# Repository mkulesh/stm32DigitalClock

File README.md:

#  "A digital clock based on STM32F405 MCU"

This repository provides hardware layout and firmware for a radio-controlled digital clock based on [STM32F405RG](http://www.st.com/content/st_com/en/products/microcontrollers/stm32-32-bit-arm-cortex-mcus/stm32-high-performance-mcus/stm32f4-series/stm32f405-415/stm32f405rg.html) MCU and [DCF77](https://de.wikipedia.org/wiki/DCF77) receiver:

## Hardware design
This clock consist of two boards:
- the first display board contains four 0.8 inch. single digit numerical displays, one 2x16 chars LCD-display, and four buttons that allow to adjust current time, three alarms and some settings:

- the second board contains STM32F405 MCU with a lot of periphery: DC connector, voltage regulators, HSE and LSE crystals, JTAG programming connector, light sensor, temperature sensor, DCF77 receiver with ferrite core, SD card connector, DAC and audio amplifier for primary WAV-based alarm, outputs for audio speakers, one piezo buzzer for the secondary alarm, UART-USB bridge and USB connector (used for debugging purposes):

PCB are developed in Eagle CAD (see directory pcb):

## Firmware
The firmware (see directory src) is written in C++ [System Workbench for STM32](http://www.st.com/en/development-tools/sw4stm32.html). It is based on HAL library, FatFS and the second object-oriented abstraction layer called *StmPlusPlus* that implements high-level access for all used hardware components. *StmPlusPlus* also contains WAV-streamer (16 bit stereo, 44kHz) and [DCF77](https://de.wikipedia.org/wiki/DCF77) receiver with a special windowed filter used to improce signal quality.

## There are some known problems in this project
- DCF77 receiver heeds some time a pair of hours to capture the time stamp. 
- Wrong position of the DC and USB connector: access to the connector is blocked by audio speakers
- Level of the input signal for the audio amplifier is too high. 

## License
This software is published under the *GNU General Public License, Version 3*

Copyright (C) 2016-2017 Mikhail Kulesh

This program is free software: you can redistribute it and/or modify it under the terms of the GNU General Public License as published by the Free Software Foundation, either version 3 of the License, or (at your option) any later version.

This program is distributed in the hope that it will be useful, but WITHOUT ANY WARRANTY; without even the implied warranty of MERCHANTABILITY or FITNESS FOR A PARTICULAR PURPOSE.  See the GNU General Public License for more details. You should have received a copy of the GNU General Public License along with this program.

If not, see [www.gnu.org/licenses](http://www.gnu.org/licenses).

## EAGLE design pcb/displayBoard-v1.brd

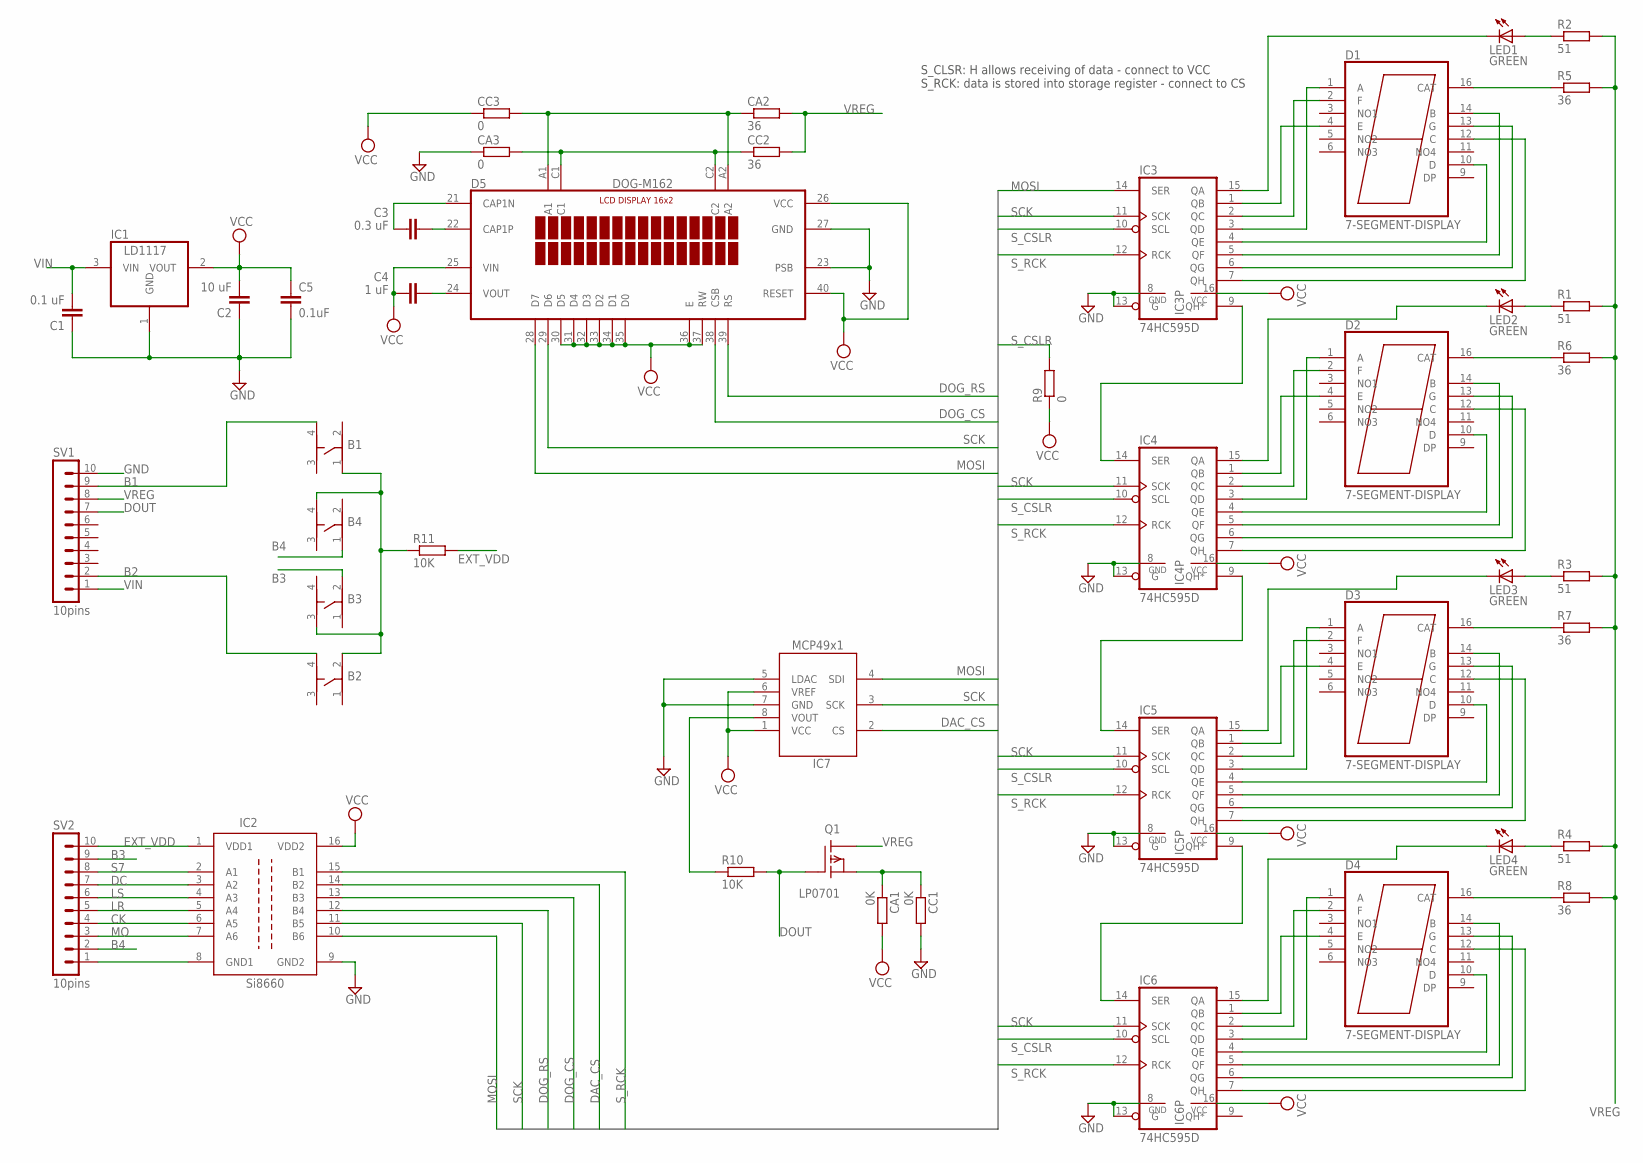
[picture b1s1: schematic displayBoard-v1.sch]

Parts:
B1, B2, B3, B4: BUTTON-D6X
C1: 0.1 uF; C1206
C2: 10 uF; C1206
C3: 0.3 uF; C1206
C4: 1 uF; C1206
C5: 0.1uF; C1206
CA1: 0K; R1206
CA2: 36; R1206
CA3: 0; R1206
CC1: 0K; R1206
CC2: 36; R1206
CC3: 0; R1206
D1, D2, D3, D4: 7-SEGMENT-DISPLAY; LDS-A812
D5: DOG-M162; DOGM162
IC1: LD1117; SOT223
IC2: SI-8660; SOP-16
IC3, IC4, IC5, IC6: 74HC595D; SO16
IC7: MCP4921; MSOP-8
LED1, LED2, LED3, LED4: GREEN; LED3MM
Q1: LP0701; TO-92
R1, R2, R3, R4: 51; R1206
R5, R6, R7, R8: 36; R1206
R9: 0; R1206
R10, R11: 10K; R1206
SV1, SV2: 10pins; MA10-1

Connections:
B1: B1.4, SV1.9
B2: B2.4, SV1.2
B3: B3.2, SV2.9
B4: B4.1, SV2.2
CK: IC2.6 (A5), SV2.4
DAC_CS: IC2.14 (B2), IC7.2 (CS)
DC: IC2.3 (A2), SV2.7
DOG_CS: D5.38 (CSB), IC2.13 (B3)
DOG_RS: D5.39 (RS), IC2.12 (B4)
DOUT: Q1.2 (G), R10.2, SV1.7
EXT_VDD: IC2.1 (VDD1), R11.2, SV2.10
GND: C1.1, C2.1, C5.2, CA3.1, CC1.2, D5.23 (PSB), D5.27 (GND), IC1.1 (GND), IC2.9 (GND2), IC3.8 (GND), IC3.13 (G), IC4.8 (GND), IC4.13 (G), IC5.8 (GND), IC5.13 (G), IC6.8 (GND), IC6.13 (G), IC7.5 (LDAC), IC7.7 (GND), SV1.10
LR: IC2.5 (A4), SV2.5
LS: IC2.4 (A3), SV2.6
MO: IC2.7 (A6), SV2.3
MOSI: D5.28 (D7), IC2.10 (B6), IC3.14 (SER), IC7.4 (SDI)
unnamed: D1.12 (C), IC3.7 (QH)
unnamed: D2.4 (E), IC4.1 (QB)
unnamed: D2.1 (A), IC4.3 (QD)
unnamed: D2.10 (D), IC4.4 (QE)
unnamed: D2.13 (G), IC4.6 (QG)
unnamed: D3.4 (E), IC5.1 (QB)
unnamed: D3.2 (F), IC5.2 (QC)
unnamed: D3.1 (A), IC5.3 (QD)
unnamed: D3.13 (G), IC5.6 (QG)
unnamed: D3.12 (C), IC5.7 (QH)
unnamed: D4.4 (E), IC6.1 (QB)
unnamed: IC2.8 (GND1), SV2.1
unnamed: B1.1, B2.2, B3.3, B4.4, R11.1
unnamed: LED4.A, R4.1
unnamed: LED3.A, R3.1
unnamed: IC6.15 (QA), LED4.K (C)
unnamed: IC7.8 (VOUT), R10.1
unnamed: IC5.15 (QA), LED3.K (C)
unnamed: IC4.15 (QA), LED2.K (C)
unnamed: D1.4 (E), IC3.1 (QB)
unnamed: D1.2 (F), IC3.2 (QC)
unnamed: LED2.A, R1.1
unnamed: D1.1 (A), IC3.3 (QD)
unnamed: D1.10 (D), IC3.4 (QE)
unnamed: D1.14 (B), IC3.5 (QF)
unnamed: D1.13 (G), IC3.6 (QG)
unnamed: D2.2 (F), IC4.2 (QC)
unnamed: D2.14 (B), IC4.5 (QF)
unnamed: D2.12 (C), IC4.7 (QH)
unnamed: IC3.9 (QH*), IC4.14 (SER)
unnamed: D3.10 (D), IC5.4 (QE)
unnamed: D3.14 (B), IC5.5 (QF)
unnamed: D4.2 (F), IC6.2 (QC)
unnamed: D4.1 (A), IC6.3 (QD)
unnamed: D4.10 (D), IC6.4 (QE)
unnamed: D4.14 (B), IC6.5 (QF)
unnamed: D4.13 (G), IC6.6 (QG)
unnamed: D4.12 (C), IC6.7 (QH)
unnamed: IC5.9 (QH*), IC6.14 (SER)
unnamed: IC4.9 (QH*), IC5.14 (SER)
unnamed: D1.16 (CAT), R5.1
unnamed: D2.16 (CAT), R6.1
unnamed: D3.16 (CAT), R7.1
unnamed: D4.16 (CAT), R8.1
unnamed: IC3.15 (QA), LED1.K (C)
unnamed: LED1.A, R2.1
unnamed: CA1.1, CC1.1, Q1.1 (S)
unnamed: CA2.1, CC3.2, D5.A1, D5.A2
unnamed: C3.1, D5.21 (CAP1N)
unnamed: C3.2, D5.22 (CAP1P)
unnamed: C4.1, D5.24 (VOUT)
unnamed: CA3.2, CC2.1, D5.C1, D5.C2
S7: IC2.2 (A1), SV2.8
SCK: D5.29 (D6), IC2.11 (B5), IC3.11 (SCK), IC4.11 (SCK), IC5.11 (SCK), IC6.11 (SCK), IC7.3 (SCK)
S_CSLR: IC3.10 (SCL), IC4.10 (SCL), IC5.10 (SCL), IC6.10 (SCL), R9.2
S_RCK: IC2.15 (B1), IC3.12 (RCK), IC4.12 (RCK), IC5.12 (RCK), IC6.12 (RCK)
VCC: C2.2, C4.2, C5.1, CA1.2, CC3.1, D5.25 (VIN), D5.26 (VCC), D5.30 (D5), D5.31 (D4), D5.32 (D3), D5.33 (D2), D5.34 (D1), D5.35 (D0), D5.36 (E), D5.37 (RW), D5.40 (RESET), IC1.2 (VOUT), IC2.16 (VDD2), IC3.16 (VCC), IC4.16 (VCC), IC5.16 (VCC), IC6.16 (VCC), IC7.1 (VCC), IC7.6 (VREF), R9.1
VIN: C1.2, IC1.3 (VIN), SV1.1
VREG: CA2.2, CC2.2, Q1.3 (D), R1.2, R2.2, R3.2, R4.2, R5.2, R6.2, R7.2, R8.2, SV1.8

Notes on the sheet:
S_CLSR: H allows receiving of data - connect to VCC S_RCK: data is stored into storage register - connect to CS

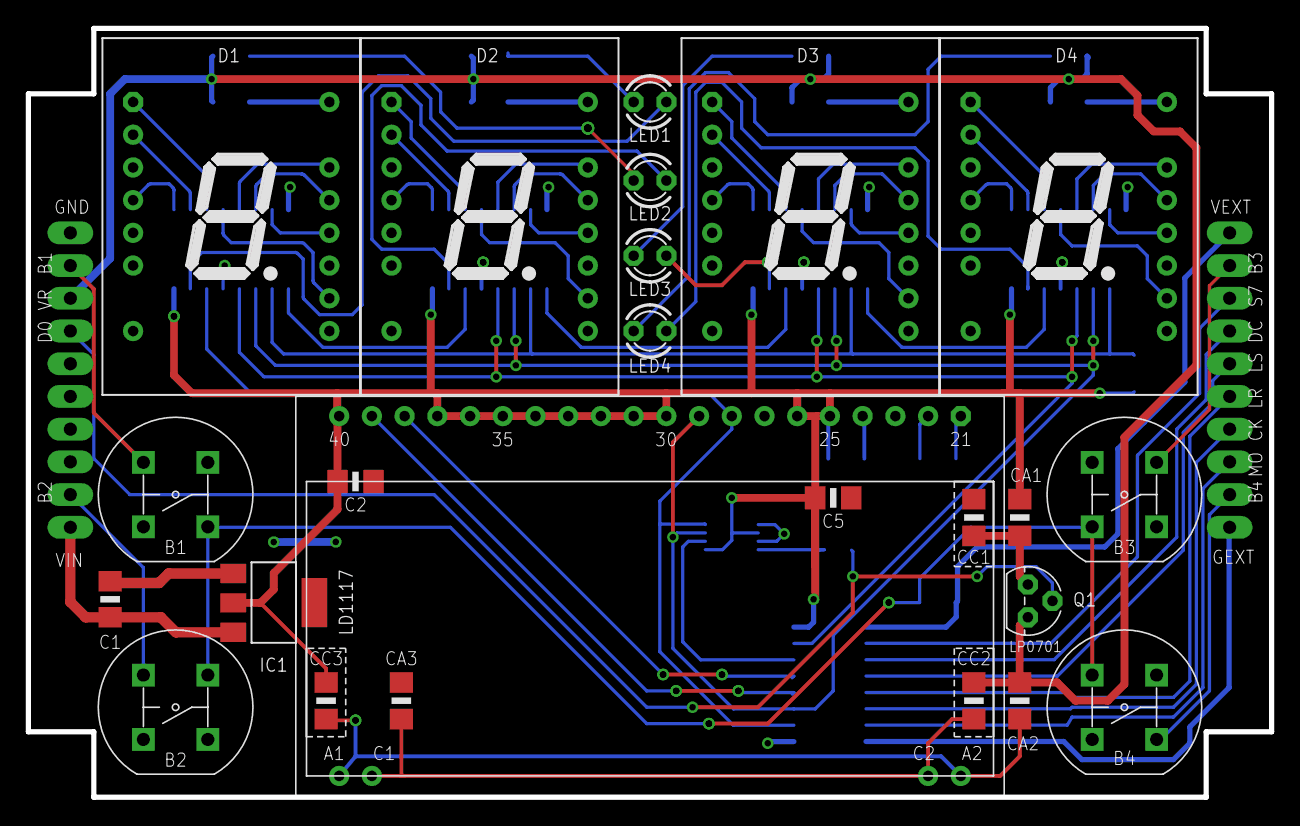
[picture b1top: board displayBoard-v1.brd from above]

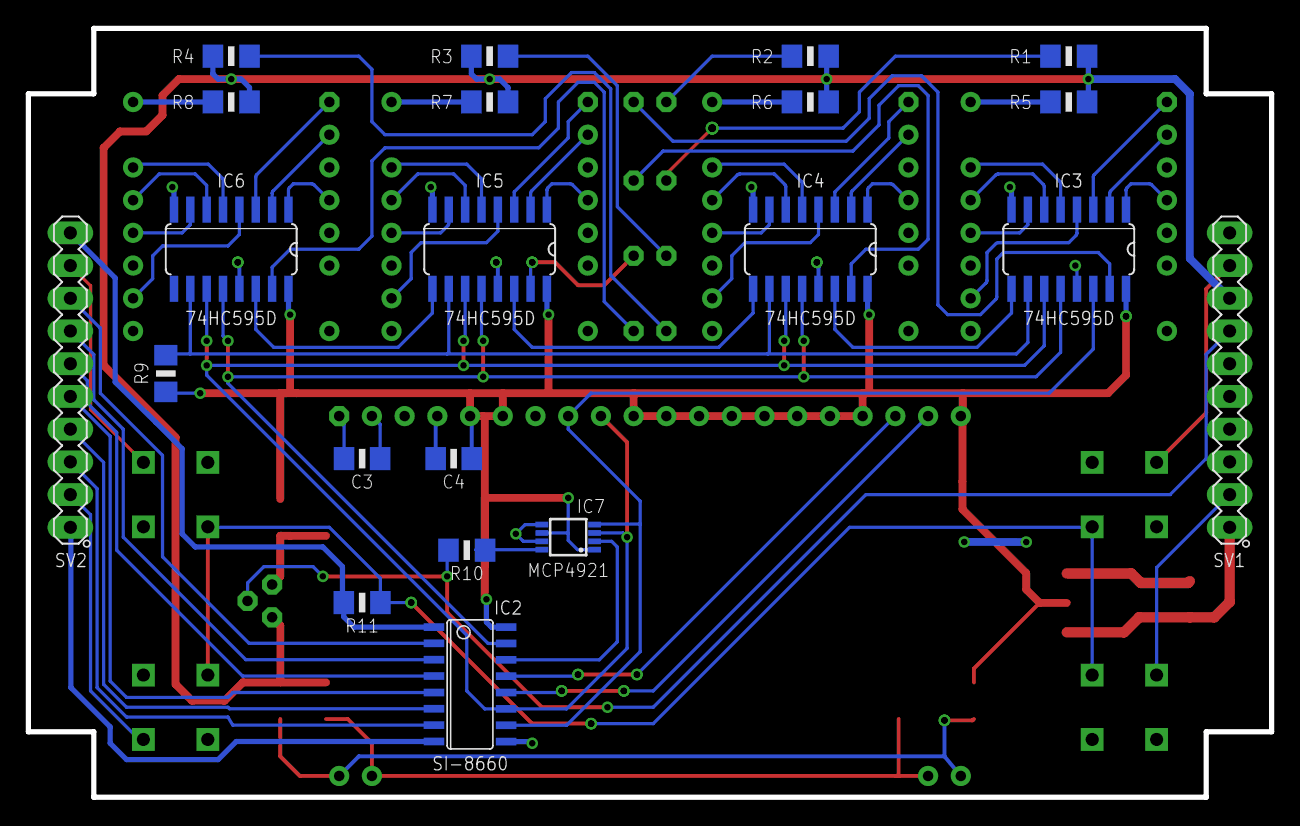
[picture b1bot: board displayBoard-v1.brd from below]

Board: 2 copper layers, 96.5 x 59.7 mm, 45 parts (21 on the bottom side), 75 nets.

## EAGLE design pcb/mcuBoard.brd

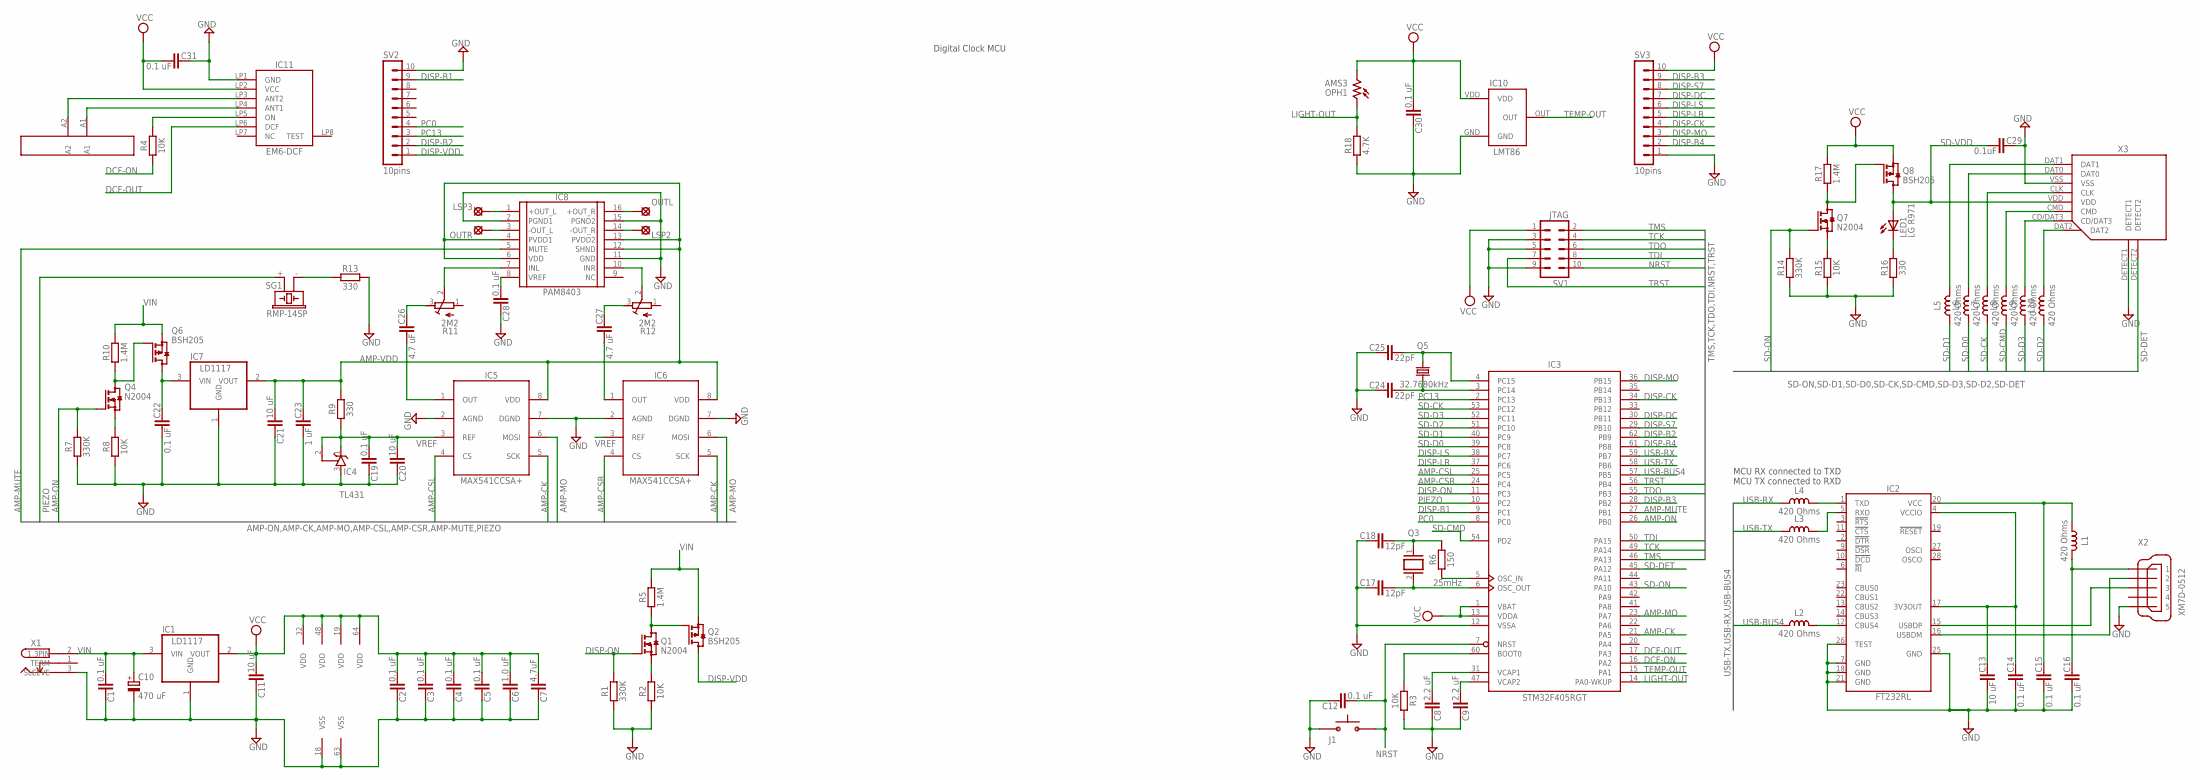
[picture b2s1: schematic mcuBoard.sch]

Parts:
A1: DCF77-ANT
C1, C2, C3, C4, C5, C12, C14, C15, C16, C19, C22, C28, C30, C31: 0.1 uF; C1206
C6: 1.0 uF; C1206
C7: 4.7uF; C1206
C8, C9: 2.2 uF; C1206
C10: 470 uF; TT5D11L
C11, C13, C20, C21: 10 uF; C1206
C17, C18: 12pF; C1206
C23: 1 uF; C1206
C24, C25: 22pF; C1206
C26, C27: 4.7 uF; C1206
C29: 0.1uF; C1206
IC1, IC7: LD1117; SOT223
IC2: FT232RL; SSOP28
IC3: STM32F405RGT; LQFP64
IC4: TL431; SOT-23
IC5, IC6: MAX541CCSA+; SOIC-8
IC8: PAM8403; SOP-16
IC10: LMT86
IC11: DCF77
J1: BUTTON-FSM14JRT
L1, L2, L3, L4, L5, L6, L7, L8, L9, L10: 420 Ohms; L0603
LED1: LG R971; CHIP-LED0805
LSP2, LSP3: LSP10
OPH1: AMS3; VT900
OUTL: LSP10
OUTR: LSP10
Q1, Q4, Q7: N2004; SOT23
Q2, Q6, Q8: BSH205; SOT23
Q3: 25mHz; HC-46X
Q5: 32.7680kHz; MC-306
R1, R7, R14: 330K; R1206
R2, R3, R4, R8, R15: 10K; R1206
R5, R10, R17: 1.4M; R1206
R6: 150; R1206
R9, R13, R16: 330; R1206
R11, R12: 2M2; R-TRIM-3362U
R18: 4.7K; R1206
SG1: RMP-14SP; F/CM12P
SV1: JTAG; MA05-2
SV2, SV3: 10pins; MA10-1
X1: DC-8N; BUCHSE-1.3X3.75
X2: XM7D-0512
X3: MICRO-SD-DM3AT; DM3AT

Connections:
AMP-CK: IC3.21 (PA5), IC5.5 (SCK), IC6.5 (SCK)
AMP-CSL: IC3.25 (PC5), IC5.4 (CS)
AMP-CSR: IC3.24 (PC4), IC6.4 (CS)
AMP-MO: IC3.23 (PA7), IC5.6 (MOSI), IC6.6 (MOSI)
AMP-MUTE: IC3.27 (PB1), IC8.5 (MUTE)
AMP-ON: IC3.26 (PB0), Q4.1 (G), R7.2
AMP-VDD: C21.2, C23.1, IC5.8 (VDD), IC6.8 (VDD), IC7.2 (VOUT), IC8.4 (PVDD1), IC8.6 (VDD), IC8.12 (SHND), IC8.13 (PVDD2), R9.2
BOOT: IC3.60 (BOOT0), R3.1
DAC_OUTR: C27.2, IC6.1 (OUT)
DCF-ON: IC3.16 (PA2), R4.1
DCF-OUT: IC3.17 (PA3), IC11.LP6 (DCF)
DISP-B1: IC3.9 (PC1), SV2.9
DISP-B2: IC3.62 (PB9), SV2.2
DISP-B3: IC3.28 (PB2), SV3.9
DISP-B4: IC3.61 (PB8), SV3.2
DISP-CK: IC3.34 (PB13), SV3.4
DISP-DC: IC3.30 (PB11), SV3.7
DISP-LR: IC3.37 (PC6), SV3.5
DISP-LS: IC3.38 (PC7), SV3.6
DISP-MO: IC3.36 (PB15), SV3.3
DISP-ON: IC3.11 (PC3), Q1.1 (G), R1.2
DISP-S7: IC3.29 (PB10), SV3.8
DISP-VDD: Q2.3 (D), SV2.1
D_VG: Q7.3 (D), Q8.1 (G), R17.1
D_VG1: Q4.3 (D), Q6.1 (G), R10.1
D_VG2: Q1.3 (D), Q2.1 (G), R5.1
GND: C1.1, C2.1, C3.1, C4.1, C5.1, C6.1, C7.1, C8.1, C9.1, C10.-, C11.1, C12.1, C13.2, C14.2, C15.2, C16.2, C17.1, C18.1, C19.1, C20.1, C21.1, C22.2, C23.2, C24.1, C25.1, C28.1, C29.1, C30.1, C31.1, IC1.1 (GND), IC2.7 (GND), IC2.18 (GND), IC2.21 (GND), IC2.25 (GND), IC2.26 (TEST), IC3.12 (VSSA), IC3.18 (VSS), IC3.63 (VSS), IC4.3 (A), IC5.2 (AGND), IC5.7 (DGND), IC6.2 (AGND), IC6.7 (DGND), IC7.1 (GND), IC8.2 (PGND1), IC8.11 (GND), IC8.15 (PGND2), IC10.GND, IC11.LP1 (GND), J1.P$1 (1), R1.1, R2.1, R3.2, R7.1, R8.1, R13.2, R14.1, R15.1, R16.1, R18.1, SV1.3, SV1.5, SV1.9, SV2.10, SV3.1, X1.3 (SLEEVE), X2.5, X3.DETECT1, X3.VSS
LIGHT-OUT: IC3.14 (PA0-WKUP), OPH1.1, R18.2
unnamed: IC3.5 (OSC_IN), R6.1
unnamed: A1.A1, IC11.LP4 (ANT1)
unnamed: A1.A2, IC11.LP3 (ANT2)
unnamed: L10.2, X3.DAT2
unnamed: L9.2, X3.CD/DAT3
unnamed: L8.2, X3.CMD
unnamed: L7.2, X3.CLK
unnamed: L6.2, X3.DAT0
unnamed: L5.2, X3.DAT1
unnamed: Q4.2 (S), R8.2
unnamed: C26.2, IC5.1 (OUT)
unnamed: IC8.16 (+OUT_R), OUTL.MP
unnamed: C26.1, R11.3
unnamed: C28.2, IC8.8 (VREF)
unnamed: C27.1, R12.3
unnamed: R13.1, SG1.- (2)
unnamed: C22.1, IC7.3 (VIN), Q6.3 (D)
unnamed: C16.1, L1.2, X2.1
unnamed: C15.1, IC2.20 (VCC), L1.1
unnamed: C13.1, C14.1, IC2.4 (VCCIO), IC2.17 (3V3OUT)
unnamed: IC2.16 (USBDM), X2.2
unnamed: IC2.15 (USBDP), X2.3
unnamed: IC2.1 (TXD), L4.2
unnamed: IC2.5 (RXD), L3.2
unnamed: IC2.12 (CBUS4), L2.1
unnamed: Q1.2 (S), R2.2
unnamed: C18.2, Q3.1, R6.2
unnamed: C17.2, IC3.6 (OSC_OUT), Q3.2
unnamed: IC11.LP5 (ON), R4.2
unnamed: LED1.C, R16.2
unnamed: Q7.2 (S), R15.2
unnamed: IC8.1 (+OUT_L), LSP3.MP
unnamed: IC8.3 (-OUT_L), OUTR.MP
unnamed: IC8.14 (-OUT_R), LSP2.MP
unnamed: IC8.7 (INL), R11.2
unnamed: IC8.10 (INR), R12.2
NRST: C12.2, IC3.7 (NRST), J1.P$2 (2), SV1.10
PC0: IC3.8 (PC0), SV2.4
PC13: IC3.2 (PC13), SV2.3
PIEZO: IC3.10 (PC2), SG1.+ (1)
Q2M: C24.2, IC3.3 (PC14), Q5.1
Q2P: C25.2, IC3.4 (PC15), Q5.4 (2)
SD-CK: IC3.53 (PC12), L7.1
SD-CMD: IC3.54 (PD2), L8.1
SD-D0: IC3.39 (PC8), L6.1
SD-D1: IC3.40 (PC9), L5.1
SD-D2: IC3.51 (PC10), L10.1
SD-D3: IC3.52 (PC11), L9.1
SD-DET: IC3.45 (PA12), X3.DETECT2
SD-ON: IC3.43 (PA10), Q7.1 (G), R14.2
SD-VDD: C29.2, LED1.A, Q8.3 (D), X3.VDD
TCK: IC3.49 (PA14), SV1.4
TDI: IC3.50 (PA15), SV1.8
TDO: IC3.55 (PB3), SV1.6
TEMP-OUT: IC3.15 (PA1), IC10.OUT
TMS: IC3.46 (PA13), SV1.2
TRST: IC3.56 (PB4), SV1.7
USB-BUS4: IC3.57 (PB5), L2.2
USB-RX: IC3.59 (PB7), L4.1
USB-TX: IC3.58 (PB6), L3.1
VCAP1: C8.2, IC3.31 (VCAP1)
VCAP2: C9.2, IC3.47 (VCAP2)
VCC: C2.2, C3.2, C4.2, C5.2, C6.2, C7.2, C11.2, C30.2, C31.2, IC1.2 (VOUT), IC3.1 (VBAT), IC3.13 (VDDA), IC3.19 (VDD), IC3.32 (VDD), IC3.48 (VDD), IC3.64 (VDD), IC10.VDD, IC11.LP2 (VCC), OPH1.2, Q8.2 (S), R17.2, SV1.1, SV3.10
VIN: C1.2, C10.+, IC1.3 (VIN), Q2.2 (S), Q6.2 (S), R5.2, R10.2, X1.2 (1.3PIN)
VREF: C19.2, C20.2, IC4.1 (C), IC4.2 (R), IC5.3 (REF), IC6.3 (REF), R9.1

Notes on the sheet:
MCU RX connected to TXD MCU TX connected to RXD
Digital Clock MCU

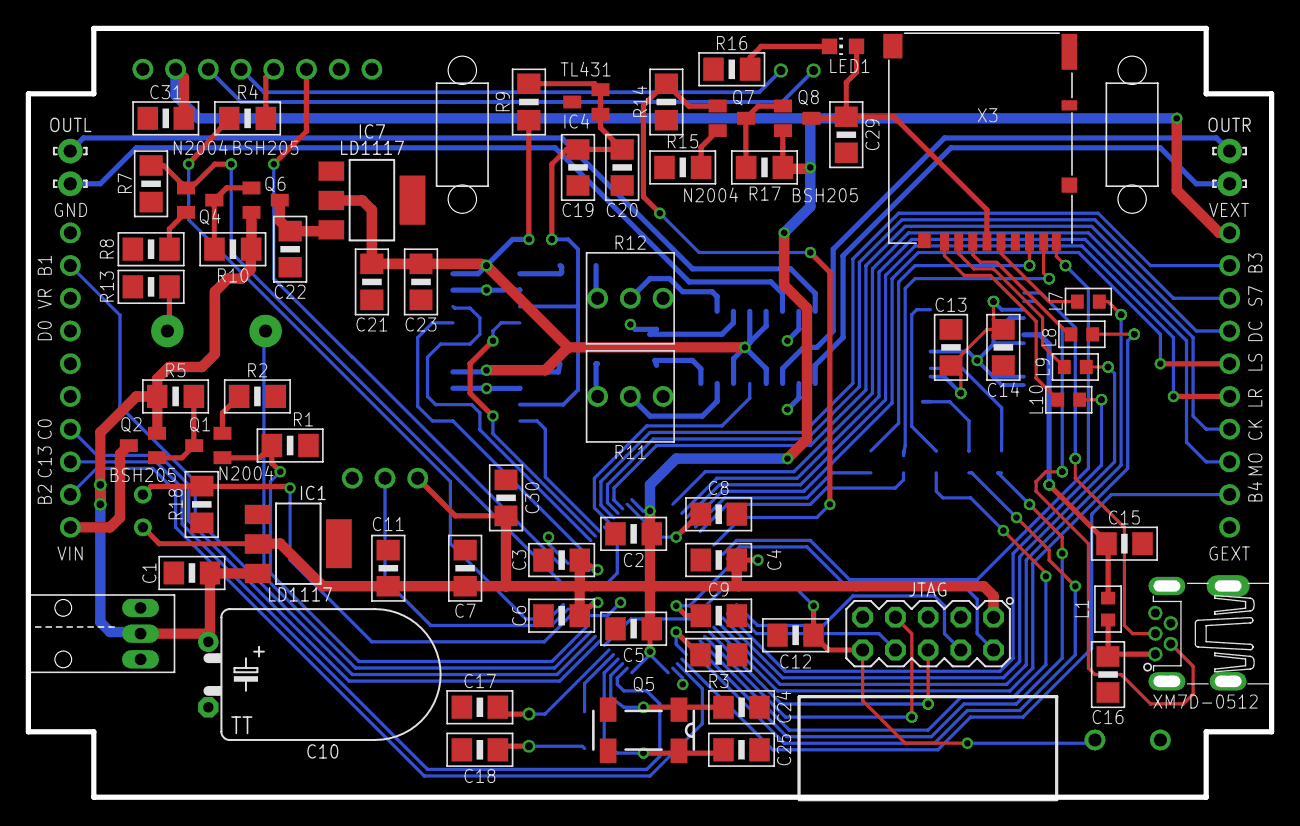
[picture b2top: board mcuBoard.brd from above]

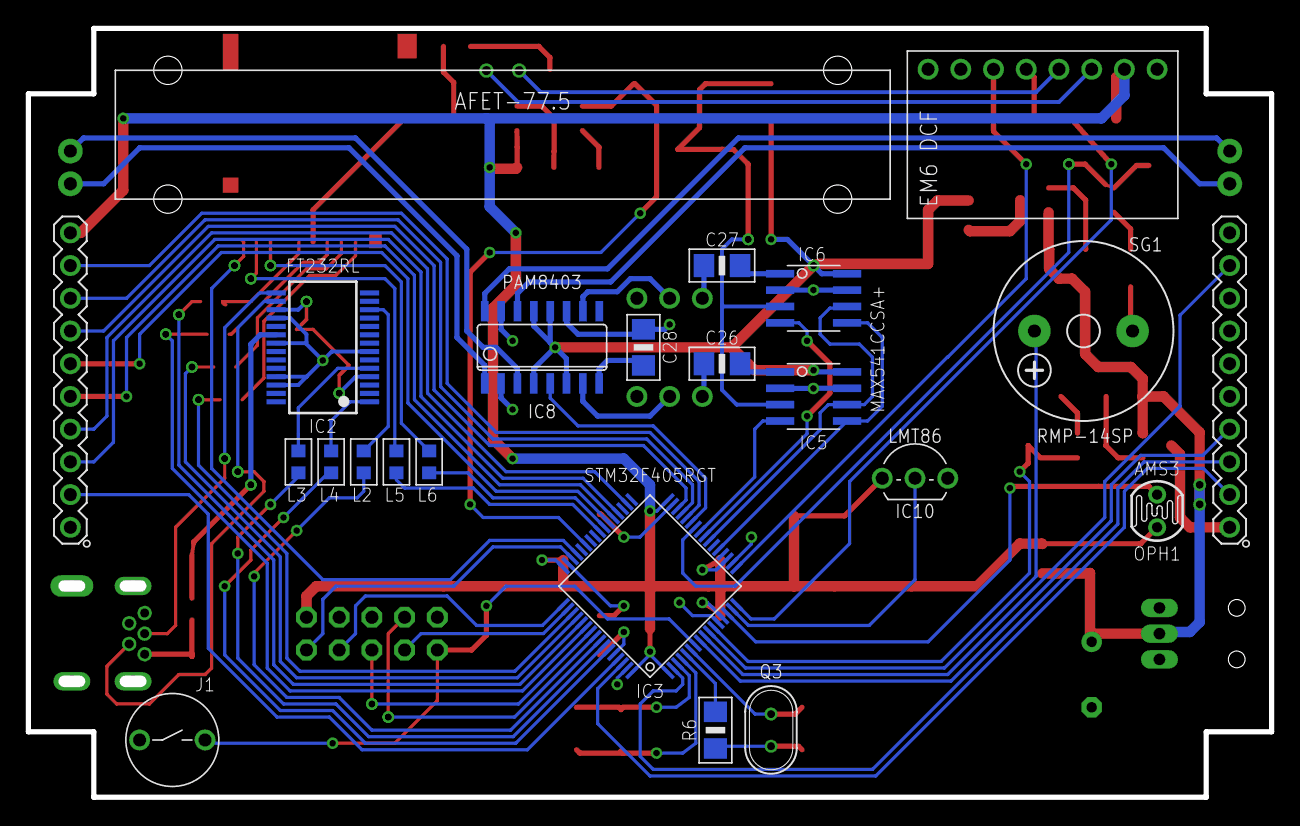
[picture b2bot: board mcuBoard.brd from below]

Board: 2 copper layers, 96.0 x 59.2 mm, 92 parts (23 on the bottom side), 93 nets.

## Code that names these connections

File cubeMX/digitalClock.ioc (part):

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Mcu.Name=STM32F405RGTx
Mcu.Package=LQFP64
Mcu.UserName=STM32F405RGTx
PA0-WKUP.GPIOParameters=GPIO_Label
PA0-WKUP.GPIO_Label=adcBrightness
PA0-WKUP.Signal=ADCx_IN0
PA1.GPIOParameters=GPIO_Label
PA1.GPIO_Label=adcTemperature
PA1.Signal=ADCx_IN1
PA10.GPIOParameters=GPIO_Label
PA10.GPIO_Label=pinSdPower
PA10.Signal=GPIO_Output
PA11.GPIOParameters=GPIO_Label
PA11.GPIO_Label=pinWavSample
PA11.Signal=GPIO_Output
PA12.GPIOParameters=GPIO_Label
PA12.GPIO_Label=pinSdDetect
PA12.Signal=GPIO_Input
PA13.Mode=JTAG(5-pin)
PA13.Signal=SYS_JTMS-SWDIO
PA14.Mode=JTAG(5-pin)
PA14.Signal=SYS_JTCK-SWCLK
PA15.Mode=JTAG(5-pin)
PA15.Signal=SYS_JTDI
PA2.GPIOParameters=GPIO_Label
PA2.GPIO_Label=pinDcfPower
PA2.Signal=GPIO_Output
PA3.GPIOParameters=GPIO_Label
PA3.GPIO_Label=pinDcfInput
PA3.Signal=GPIO_Input
PA4.Signal=SPI1_NSS
PA5.Mode=Full_Duplex_Master
PA5.Signal=SPI1_SCK
PA6.Mode=Full_Duplex_Master
PA6.Signal=SPI1_MISO
PA7.Mode=Full_Duplex_Master
PA7.Signal=SPI1_MOSI
PB0.GPIOParameters=GPIO_Label
PB0.GPIO_Label=pinAmpPower
PB0.Signal=GPIO_Output
PB1.GPIOParameters=GPIO_Label
PB1.GPIO_Label=pinAmpMute
PB1.Signal=GPIO_Output
PB10.GPIOParameters=GPIO_Label
PB10.GPIO_Label=pinSsdCs
PB10.Signal=GPIO_Output
PB11.GPIOParameters=GPIO_Label
PB11.GPIO_Label=pinHmiBrightnessCs
PB11.Signal=GPIO_Output
PB12.Signal=SPI2_NSS
PB13.Mode=Full_Duplex_Master
PB13.Signal=SPI2_SCK
PB14.Mode=Full_Duplex_Master
PB14.Signal=SPI2_MISO
PB15.Mode=Full_Duplex_Master
PB15.Signal=SPI2_MOSI
PB2.GPIOParameters=GPIO_Label
PB2.GPIO_Label=bPlus
PB2.Signal=GPIO_Input
PB3.Mode=JTAG(5-pin)
PB3.Signal=SYS_JTDO-SWO
PB4.Mode=JTAG(5-pin)
PB4.Signal=SYS_JTRST
PB5.GPIOParameters=GPIO_Label
PB5.GPIO_Label=pinUsbVoltage
PB5.Signal=GPIO_Input
PB6.Mode=Asynchronous
PB6.Signal=USART1_TX
PB7.Mode=Asynchronous
PB7.Signal=USART1_RX
PB8.GPIOParameters=GPIO_Label
PB8.GPIO_Label=bMinus
PB8.Signal=GPIO_Output
PB9.GPIOParameters=GPIO_Label
PB9.GPIO_Label=bActiveElement
PB9.Signal=GPIO_Input
PC1.GPIOParameters=GPIO_Label
PC1.GPIO_Label=bMode
PC1.Signal=GPIO_Input
PC10.Mode=SD_4_bits_Wide_bus
PC10.Signal=SDIO_D2
PC11.Mode=SD_4_bits_Wide_bus
PC11.Signal=SDIO_D3
PC12.Mode=SD_4_bits_Wide_bus
PC12.Signal=SDIO_CK
PC14-OSC32_IN.Mode=LSE-External-Oscillator
PC14-OSC32_IN.Signal=RCC_OSC32_IN
PC15-OSC32_OUT.Mode=LSE-External-Oscillator
PC15-OSC32_OUT.Signal=RCC_OSC32_OUT
PC2.GPIOParameters=GPIO_Label
PC2.GPIO_Label=piezoAlarm
PC2.Signal=GPIO_Output
PC3.GPIOParameters=GPIO_Label
PC3.GPIO_Label=pinHmiPower
PC3.Signal=GPIO_Output
PC4.GPIOParameters=GPIO_Label
PC4.GPIO_Label=pinRightChannel
PC4.Signal=GPIO_Output
PC5.GPIOParameters=GPIO_Label
PC5.GPIO_Label=pinLeftChannel
PC5.Signal=GPIO_Output
PC6.GPIOParameters=GPIO_Label
PC6.GPIO_Label=pinLcdRs
PC6.Signal=GPIO_Output
PC7.GPIOParameters=GPIO_Label
PC7.GPIO_Label=pinLcdCs
PC7.Signal=GPIO_Output
PC8.Mode=SD_4_bits_Wide_bus
PC8.Signal=SDIO_D0
PC9.Mode=SD_4_bits_Wide_bus
PC9.Signal=SDIO_D1
PD2.Mode=SD_4_bits_Wide_bus
PD2.Signal=SDIO_CMD
PH0-OSC_IN.Mode=HSE-External-Oscillator
PH0-OSC_IN.Signal=RCC_OSC_IN
PH1-OSC_OUT.Mode=HSE-External-Oscillator
PH1-OSC_OUT.Signal=RCC_OSC_OUT
RCC.HSE_VALUE=25000000
RCC.SYSCLKFreq_VALUE=168000000
RCC.SYSCLKSource=RCC_SYSCLKSOURCE_PLLCLK

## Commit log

2019-04-28 Updated PCB description
2019-04-28 Moved cubeMX model
2021-04-05 moved cubeMX files
2023-07-21 Added description

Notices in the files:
README.md:
License: GNU GPLv3
